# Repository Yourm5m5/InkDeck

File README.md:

# InkDeck

**A pocket e-paper e-reader with physical page-turn buttons, weeks of battery life, and books loaded over Wi-Fi.**

## What is InkDeck?

InkDeck is a DIY e-reader about the size of a paperback (153 × 72 × 23.5 mm). It has a 4.7" e-paper screen that looks like printed paper, so it's easy on the eyes and readable in sunlight, and it keeps the page on screen even with the power off.

It's built around a **LilyGo T5 4.7" E-Paper S3** board (ESP32-S3 + 960 × 540 e-paper + microSD slot), plus a **custom grip PCB I designed in KiCad**. The grip board sits beside the screen under your right thumb and has:

- **3 buttons**: PREV, NEXT and MENU
- **A coin vibration motor** for a little buzz on each page turn
- **A slide power switch** between the battery and the LilyGo

It reads **EPUB** and **.txt** books from the microSD card, and you can add books from your phone over Wi-Fi without taking the card out. Everything fits in a 3D-printed case I modelled in Fusion 360.

---

## Why I built it

I like reading on e-paper, but most e-readers only work properly with one company's book store, and the cheaper ones only have a touchscreen. I wanted **real buttons** I can press with one thumb while holding it in one hand, like turning a page.

Building it myself means it reads my own DRM-free books (Project Gutenberg, Standard Ebooks) with no account or store. I can also change anything I want, from how long the buttons are held to how the pages look.

It was also a good way to learn about low-power design, which a phone or laptop never makes you think about:
- picking pins that can wake the chip from deep sleep
- dealing with strapping pins
- making e-paper and a battery work together

---

## Features

- 4.7" 960 × 540 e-paper with 16 grey levels: easy to read, and the page stays on screen with zero power
- Reads **EPUB** (converted once, then opens instantly) and **.txt** books
- **Physical buttons**: tap for the next or previous page, hold to jump a chapter
- **Haptic feedback**: a different buzz for page turns, chapter jumps, errors and sleep
- **Deep sleep** after 10 minutes, then MENU wakes it on the same page
- **Wi-Fi upload**: the reader makes its own hotspot, so a phone can add or delete books
- Remembers your page in every book
- Battery % in the footer, and it shows "please charge" and sleeps when nearly flat
- One-handed grip with the buttons under your thumb

---

## How it works

```mermaid
flowchart LR
    subgraph Grip["Grip PCB"]
        BTN["PREV / NEXT / MENU buttons"]
        MOT["Vibration motor via AO3400"]
        SW["Power switch"]
    end
    subgraph LilyGo["LilyGo T5 4.7-inch S3"]
        ESP["ESP32-S3 firmware"]
        EPD["E-paper 960 x 540"]
        SD["microSD card"]
        ADC["Battery ADC IO14"]
    end
    BAT["LiPo battery"]
    PHONE["Phone or laptop"]

    BTN -->|GPIO 10 39 48| ESP
    ESP -->|GPIO 45| MOT
    BAT --> SW --> LilyGo
    BAT -.-> ADC --> ESP
    SD <-->|SPI| ESP
    ESP -->|parallel bus| EPD
    PHONE <-->|Wi-Fi hotspot| ESP
```

The e-paper, SD card and touch use almost every GPIO on the LilyGo. Only **4 are free**, so the grip PCB uses exactly 4 signals through a 6-pin JST-SH cable:

| J3 pin | Signal | LilyGo | Why this pin |
|---|---|---|---|
| 1 | +3.3V | 3V3 | |
| 2 | GND | GND | |
| 3 | BTN_MENU | IO10 | The only free **RTC pin**, so MENU can wake the chip from deep sleep |
| 4 | BTN_PREV | IO39 | Internal pull-up |
| 5 | MOTOR | IO45 | **Strapping pin**, so the PCB has a 10k pull-down to keep it LOW at boot |
| 6 | BTN_NEXT | IO48 | Internal pull-up |

---

## Controls

| Button | While reading | In the library |
|---|---|---|
| **NEXT / PREV** | Next / previous page | Move down / up |
| **Hold NEXT / PREV** (0.7 s) | Next / previous chapter | Move 5 rows |
| **MENU** | Open the library | Open the book / vibration on or off |
| **Hold MENU 1 s** | Wi-Fi upload mode | Wi-Fi upload mode |
| **Hold MENU 3 s** | Sleep | Sleep |
| **MENU while asleep** | Wake up on the same page | |

While MENU is held, the motor buzzes at 1 s and again at 3 s, so you can feel which action you'll get before letting go.

---

## Firmware

Written in **PlatformIO (Arduino framework)** with LilyGo's e-paper library. The full explanation with diagrams and code snippets is in **[firmware/FIRMWARE.md](firmware/FIRMWARE.md)**.

| File | What it does |
|---|---|
| `config.h` | Every pin and setting in one place |
| `buttons.h` | Debounced buttons: tap, hold and long press |
| `haptic.h` | Vibration patterns |
| `epub.cpp` | Turns an EPUB into plain text |
| `main.cpp` | Screens, page layout, Wi-Fi upload, sleep and the main loop |

**EPUB reader:** an EPUB is a ZIP file full of web pages. The first time a book is opened, the firmware:
1. reads the ZIP's file list
2. finds `content.opf` (title + chapter order)
3. unzips each chapter with the decoder built into the ESP32-S3's ROM
4. removes the HTML tags and saves plain text to the SD card

After that the book opens instantly. Every chapter starts on a new page.

**Pages:** a greedy word-wrap fills each line with words until the next one doesn't fit. Where every page starts is saved on the SD card, so the footer can show `Ch 3/27   57 / 312   70%` and going back a page is instant.

**Deep sleep:** the e-paper keeps the page visible with no power, so the reader looks the same asleep. MENU wakes it:

```cpp
while (digitalRead(PIN_BTN_MENU) == LOW) delay(10);   // never sleep while MENU is held
esp_sleep_enable_ext0_wakeup(GPIO_NUM_10, 0);         // MENU wakes it up
esp_deep_sleep_start();
```

**Haptics:**

| Buzz | Meaning |
|---|---|
| 1 short | Page turn |
| 2 short | Chapter jump |
| 3 quick | Can't go further |
| 1 long | Going to sleep |

**Testing:** the parts haven't arrived yet, so the EPUB converter and a simulation of the whole firmware (fake buttons, screen and SD card) are tested on a computer, in [`firmware/pc_tests`](firmware/pc_tests).

---

## Custom PCB

Designed in KiCad: a **25 × 67 mm** two-layer grip board that sits beside the LilyGo inside the case. Power is on the front layer, button signals on the back, with ground fill on both sides. It passes DRC with **0 errors, 0 unconnected**.

- **Power:** battery in → slide switch → battery out to the LilyGo's battery socket
- **Buttons:** 3 × 6 mm tact switches. MENU has a 10k pull-up so it still works in deep sleep
- **Motor driver:** AO3400 MOSFET with a 1N4148 flyback diode and a 10k gate pull-down
- **Connector:** 6-pin JST-SH (J3) to the LilyGo GPIOs

---

## Enclosure

Modelled in Fusion 360 with **user parameters**, so it can be updated once the real parts are measured. It's 3 printed parts:

1. **Front shell:** screen window, 3 button holes lined up with the grip PCB, standoffs for the PCB, and cut-outs for the power switch, USB-C and microSD
2. **Back cover:** holds the battery behind the screen and the motor behind the grip, with a raised ridge so it's comfy to hold
3. **Button caps (×3):** plungers that reach the tact switches, with a flange so they can't fall out

The grip is on the right so your thumb reaches the buttons, and USB-C is on the left so the cable doesn't get in the way.

### Exploded view

Shows how the screen, grip PCB, battery, motor, printed parts and screws fit together. The parts list, step-by-step assembly and wiring are in **[CAD/ASSEMBLY.md](CAD/ASSEMBLY.md)**.

### Renders

> The screen window, USB-C, microSD and battery sizes are placeholders and will be checked against the real parts before the final print.

---

## Bill of materials

All parts are from **AliExpress** except the custom PCB, which comes from **JLCPCB**. Prices are **approximate AUD** and change with sales, exchange rates and shipping. Many small parts only come in packs, so you'll have spares. Where a listing has several options (value, size, pin count, pack size), pick the one in the **Part** column.

### Electronics

| # | Part | Qty | Approx. AUD | Link |
|---|---|---|---|---|
| 1 | LilyGo T5 4.7" E-Paper **S3** V2.3 (ESP32-S3, N16R8) | 1 | $65.00 | [AliExpress](https://www.aliexpress.com/item/1005004647326743.html) |
| 2 | 3.7 V LiPo battery, ~2000 mAh, ~60 × 50 × 6 mm (605060), JST-PH 2.0 | 1 | $12.00 | [AliExpress search](https://www.aliexpress.com/w/wholesale-605060-lipo-battery-jst.html) (pick 605060 with a PH 2.0 plug) |
| 3 | 10 mm coin vibration motor, 3 V (pack of 10) | 1 pack | $5.00 | [AliExpress](https://www.aliexpress.com/item/1005007703166995.html) |
| 4 | 6 × 6 mm tact switches (pack of 100) | 1 pack | $3.00 | [AliExpress](https://www.aliexpress.com/item/1005008112405709.html) |
| 5 | SS12D00 mini slide switch (pack of 20) | 1 pack | $3.00 | [AliExpress](https://www.aliexpress.com/item/1005002190531295.html) |
| 6 | AO3400 N-channel MOSFET, SOT-23 (pack of 50) | 1 pack | $3.00 | [AliExpress](https://www.aliexpress.com/item/32855231231.html) |
| 7 | 1N4148 diode (pack of 100) | 1 pack | $2.00 | [AliExpress](https://www.aliexpress.com/item/1005003237310728.html) |
| 8 | 10k resistors, 0805 (pack of 100) | 1 pack | $2.00 | [AliExpress](https://www.aliexpress.com/item/32702695904.html) |
| 9 | JST-SH 1.0 mm 6-pin connectors + pre-crimped cable | 1 set | $5.00 | [AliExpress](https://www.aliexpress.com/item/1005004098040339.html) |
| 10 | JST-PH 2.0 mm 2-pin connectors + pre-crimped cable | 1 set | $4.00 | [AliExpress](https://www.aliexpress.com/item/1005002827963237.html) |
| 11 | microSD card, 8–32 GB | 1 | $8.00 | [AliExpress](https://www.aliexpress.com/item/1005004100092905.html) |
| 12 | Custom grip PCB, 5 pcs + shipping (**JLCPCB**) | 1 order | $18.00 | [JLCPCB](https://jlcpcb.com) (upload the Gerbers in `PCB/`) |
| | **Electronics subtotal** | | **$130.00** | |

### Enclosure

| # | Part | Qty | Approx. AUD | Link |
|---|---|---|---|---|
| 13 | PLA or PETG filament (~80 g of a 1 kg roll) | 1 | $3.00 | [AliExpress](https://www.aliexpress.com/item/1005006789571723.html) |
| 14 | M2 brass heat-set inserts (need 8, pack of 50) | 1 pack | $6.00 | [AliExpress](https://www.aliexpress.com/item/1005005109518603.html) |
| 15 | M2 screw assortment (4× M2×5, 4× M2×8) | 1 kit | $6.00 | [AliExpress](https://www.aliexpress.com/item/32770172952.html) |
| 16 | Thin double-sided foam tape (holds the battery) | 1 roll | $3.00 | [AliExpress](https://www.aliexpress.com/item/1005001168622872.html) |
| | **Enclosure subtotal** | | **$18.00** | |

### Total

| | AUD |
|---|---|
| Electronics | $130.00 |
| Enclosure | $18.00 |
| **Estimated total** | **≈ $148.00** |

Charging is through the LilyGo's own USB-C port, so any phone charger and USB-C cable works.

> AliExpress listings change often. If a link stops working, search AliExpress for the exact part name in the table (e.g. "LilyGo T5 4.7 S3", "AO3400").

## Repository layout

```
InkDeck/
├── README.md
├── JOURNAL.md               ← build log, day by day
├── PCB/                     ← KiCad project + Gerbers (grip PCB)
├── CAD/
│   ├── ASSEMBLY.md          ← parts list, assembly steps, wiring
│   ├── step/  stl/          ← printable parts + assemblies
│   └── images/              ← exploded view, renders, drawing
└── firmware/
    ├── platformio.ini
    ├── FIRMWARE.md          ← how everything in the code works
    ├── src/                 ← the firmware
    └── pc_tests/            ← EPUB + firmware tests that run on a computer
```

---

---

## Acknowledgements

- [LilyGo](https://lilygo.cc) for the T5 4.7" board and the [LilyGo-EPD47](https://github.com/Xinyuan-LilyGO/LilyGo-EPD47) e-paper library
- Built with [KiCad](https://www.kicad.org/), [Fusion 360](https://www.autodesk.com/products/fusion-360) and [PlatformIO](https://platformio.org/)
- Free books: [Project Gutenberg](https://www.gutenberg.org) and [Standard Ebooks](https://standardebooks.org)
- AI assistance (Claude) was used for planning, guidance, the firmware and its tests.

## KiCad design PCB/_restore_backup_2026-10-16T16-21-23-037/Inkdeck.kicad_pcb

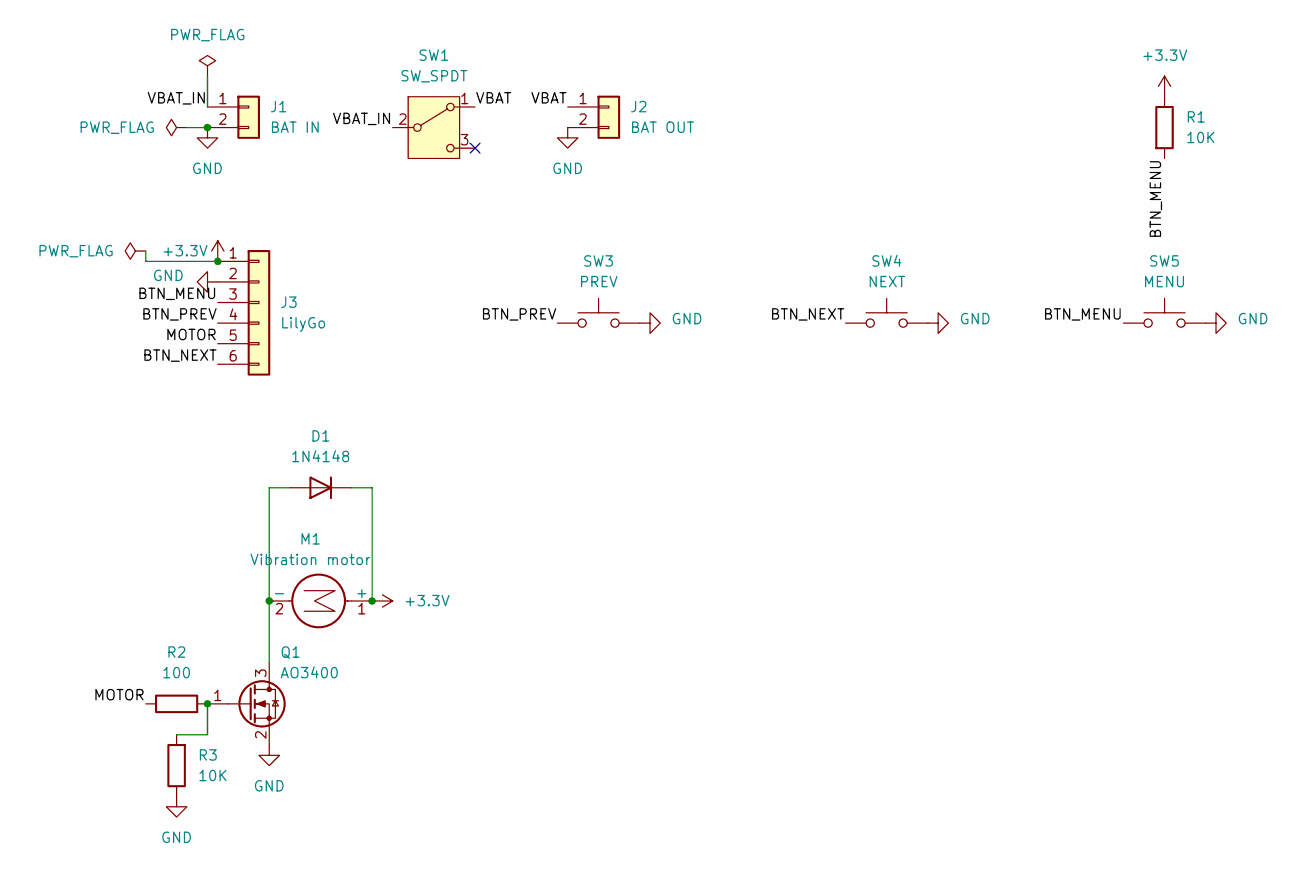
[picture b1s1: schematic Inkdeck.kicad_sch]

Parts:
D1: 1N4148; D_SOD-123
J1: BAT IN; JST_PH_S2B-PH-K_1x02_P2.00mm_Horizontal
J2: BAT OUT; JST_PH_S2B-PH-K_1x02_P2.00mm_Horizontal
J3: LilyGo; JST_SH_SM06B-SRSS-TB_1x06-1MP_P1.00mm_Horizontal
M1: Vibration motor; PinHeader_1x02_P2.54mm_Vertical
Q1: AO3400; SOT-23
R1, R3: 10K; R_0805_2012Metric
R2: 100; R_0805_2012Metric
SW1: SW_SPDT; SW_SPDT_PCM12
SW3: PREV; SW_PUSH_6mm
SW4: NEXT; SW_PUSH_6mm
SW5: MENU; SW_PUSH_6mm

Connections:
+3.3V: D1.1 (K), J3.1, M1.1 (+), R1.1
/BTN_MENU: J3.3, R1.2, SW5.1
/BTN_NEXT: J3.6, SW4.1
/BTN_PREV: J3.4, SW3.1
/MOTOR: J3.5, R2.1
/VBAT: J2.1, SW1.1 (A)
/VBAT_IN: J1.1, SW1.2 (B)
GND: J1.2, J2.2, J3.2, Q1.2 (S), R3.1, SW3.2, SW4.2, SW5.2
unnamed: D1.2 (A), M1.2 (-), Q1.3 (D)
unnamed: Q1.1 (G), R2.2, R3.2

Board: 2 copper layers, 13 parts (0 on the bottom side), 10 nets, no tracks yet.

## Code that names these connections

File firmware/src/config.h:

// =============================================================================
//  config.h – pins and settings for InkDeck
// =============================================================================
//  Everything you might want to tweak is in this one file.
#pragma once
#include <stdint.h>

// ---- Grip PCB (cable to J3) -------------------------------------------------
//   J3-1 +3.3V   J3-2 GND
//   J3-3 BTN_MENU -> IO10  (10k pull-up on the PCB, wakes from deep sleep)
//   J3-4 BTN_PREV -> IO39  (internal pull-up)
//   J3-5 MOTOR    -> IO45  (AO3400 MOSFET, 10k pull-down on the PCB)
//   J3-6 BTN_NEXT -> IO48  (internal pull-up)
#define PIN_BTN_MENU 10      // RTC-capable pin -> the only button that can wake deep sleep
#define PIN_BTN_PREV 39
#define PIN_BTN_NEXT 48
#define PIN_MOTOR    45      // strapping pin! the PCB pull-down keeps it LOW at boot

// ---- On the LilyGo board ----------------------------------------------------
#define PIN_BAT_ADC  14      // battery voltage through a 1:2 divider
#define SD_MISO 16           // microSD on its own SPI bus
#define SD_MOSI 15
#define SD_SCK  11
#define SD_CS   42

// ---- Page layout (pixels, screen is 960 x 540) ------------------------------
const int MARGIN_X   = 40;
const int MARGIN_TOP = 30;
const int FOOTER_H   = 60;   // strip at the bottom for title / page / battery
const int INDENT_PX  = 36;   // first-line indent for paragraphs (a TAB in the text)

// ---- Buttons (milliseconds) -------------------------------------------------
const uint32_t DEBOUNCE_MS   = 25;    // contacts must be stable this long to count
const uint32_t HOLD_MS       = 700;   // PREV/NEXT held this long = chapter jump
const uint32_t MENU_LONG_MS  = 1000;  // MENU held 1 s  = Wi-Fi upload
const uint32_t MENU_VLONG_MS = 3000;  // MENU held 3 s  = sleep now

// ---- Power ------------------------------------------------------------------
const uint32_t SLEEP_AFTER_MS = 10UL * 60 * 1000;  // auto deep sleep after 10 min idle
const int      LOW_BATTERY    = 3;                 // % -> show "charge me" and sleep

// ---- Haptics ----------------------------------------------------------------
const bool HAPTICS_DEFAULT = true;    // can be switched off in the library ("Vibration: on/off" row)

// ---- Cache versions (bump to force every book to be re-processed) ----------
const uint32_t INDEX_VERSION = 0x494B0003;   // page index format / layout rules
const uint32_t META_VERSION  = 0x494D0001;   // converted-EPUB cache format

// ---- Wi-Fi upload hotspot ---------------------------------------------------
#define AP_NAME "InkDeck"
#define AP_PASS "readmore1"
